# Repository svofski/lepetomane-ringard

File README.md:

# Pétomane ringard

A "simple" 3-voice "sound chip" with wavetables.

## Current status: 
 - [x] waiting for the first revision of PCB
 - [x] research implementation of USB MIDI
   - [ ] pico firmware in [sw/pico](sw/pico)
 - [x] audio level meter based on CH32V003
    - [CH32V003 specific notes](CH32V003-notes.md)
    - The code for the level meter is [here](wch-ch32v003/pio-arduino-ch32v003)
 - [x] assemble the PCB
   - [x] audio level meter
   - [x] Pi Pico host board
   - [x] main board
 - [ ] verification
   - [x] write a simple serial debug monitor
   - [x] 82c54 can be programmed, produces frequencies as expected
   - [x] counters U10, U11, U12 generate LSB addresses
     - this is hard to verify without a full logic probe (and even with one) but the counting period seems to be correct. I set ctr0 divider = 100, PITCHx256_A is 80kHz; pin U10.9 nRCO has short pulses at 312.5kHz, which is expected because 80e3/256 = 312.5
   - [ ] 82c55
   - [ ] MVOL DAC
   - [ ] WRMODE
   - [ ] LOOPEN_B (one-shot count on channel B)

## About this project

A never ending search of a simple chiptune synthesizer design that could have existed back in the 1980s. This design departs from the tech available to hobbyists in the 80s, but it's not too out there either. 

### Description in broad strokes

The master clock is 8MHz. Potentially 10MHz, but it would be pushing the capabilities of 82C54. The timer divides the main frequency and provides the pitch for the 3 channels. 

Waveforms are stored as samples in a ROM. This is essentially a short sample player. A sample is always 256 counts long, 8-bit waveform. For example, a sawtooth would be a sequence of numbers 0..255 stored in addresses 0..255. 
The ROM has 16 address bits, so there are 256 waveforms. This is how timbre and volume are set: simply by selecting 8 MSB of the sample address. It is possible to define just one waveshape and 256 amplitude levels, or for example 4 waveshapes and 64 amplitude levels for each one. Or several MSB bits could be reserved for selecting drum samples. It's a relatively flexible system.

One important remark. Because this is a frequency divider and the base frequency is only 8MHz, we don't get a good resolution if samples represent a single period. For decent musical resolution the waveforms will have to be squeezed to maybe 32 or 64 samples per period.

The 3 channels are time-multiplexed and sent to the two channels of DAC (TLC7258C) in a sequence. In order to provide a stereo mix, channels A/B/C/A/B/C are steered to channels L/L/R/L/R/R. Hopefully this will create an effect of a stereo mix where Left = A + 0.5B and Right = 0.5 + C.

There is a master volume which is just a second DAC providing reference voltage for the main DAC. If the main DAC is stopped, the master volume can be used to play back samples directly.

Channel B (central) can optionally stop after playing a sample once. This may be useful to play back short drum samples.

The MSB for channels A/B/C is set respectively in the registers A/B/C of 82C55. 

Because ROMs are a rare beast in 2024, K6X4008C1F SRAM is used instead. Only 64K of available address space is used. Loading is facilitated by the same 82C55 chip.

The external interface in the Pétomanesque tradition looks like a parallel port "ПУ" of Vector-06C, but in reality it's just a cursed three-row 2.54mm pin header. It is yet to be discovered whether this could ever be useful in a real computer or not. For now Raspberry Pi Pico will be used as a main driver for this board.

The complexity of this design surpasses the original expecation, yet remains within realm of possibility for a 80s design. SRAM in such quantities would have been wildly expensive back in the day, so a ROM could be used instead.

## Schematic/BOM
 * [https://github.com/svofski/lepetomane-ringard/tree/master/kicad/neopeto](https://kicanvas.org/?github=https%3A%2F%2Fgithub.com%2Fsvofski%2Flepetomane-ringard%2Ftree%2Fmaster%2Fkicad%2Fneopeto)
 * [ibom](https://svofski.github.io/lepetomane-ringard/ibom.html)

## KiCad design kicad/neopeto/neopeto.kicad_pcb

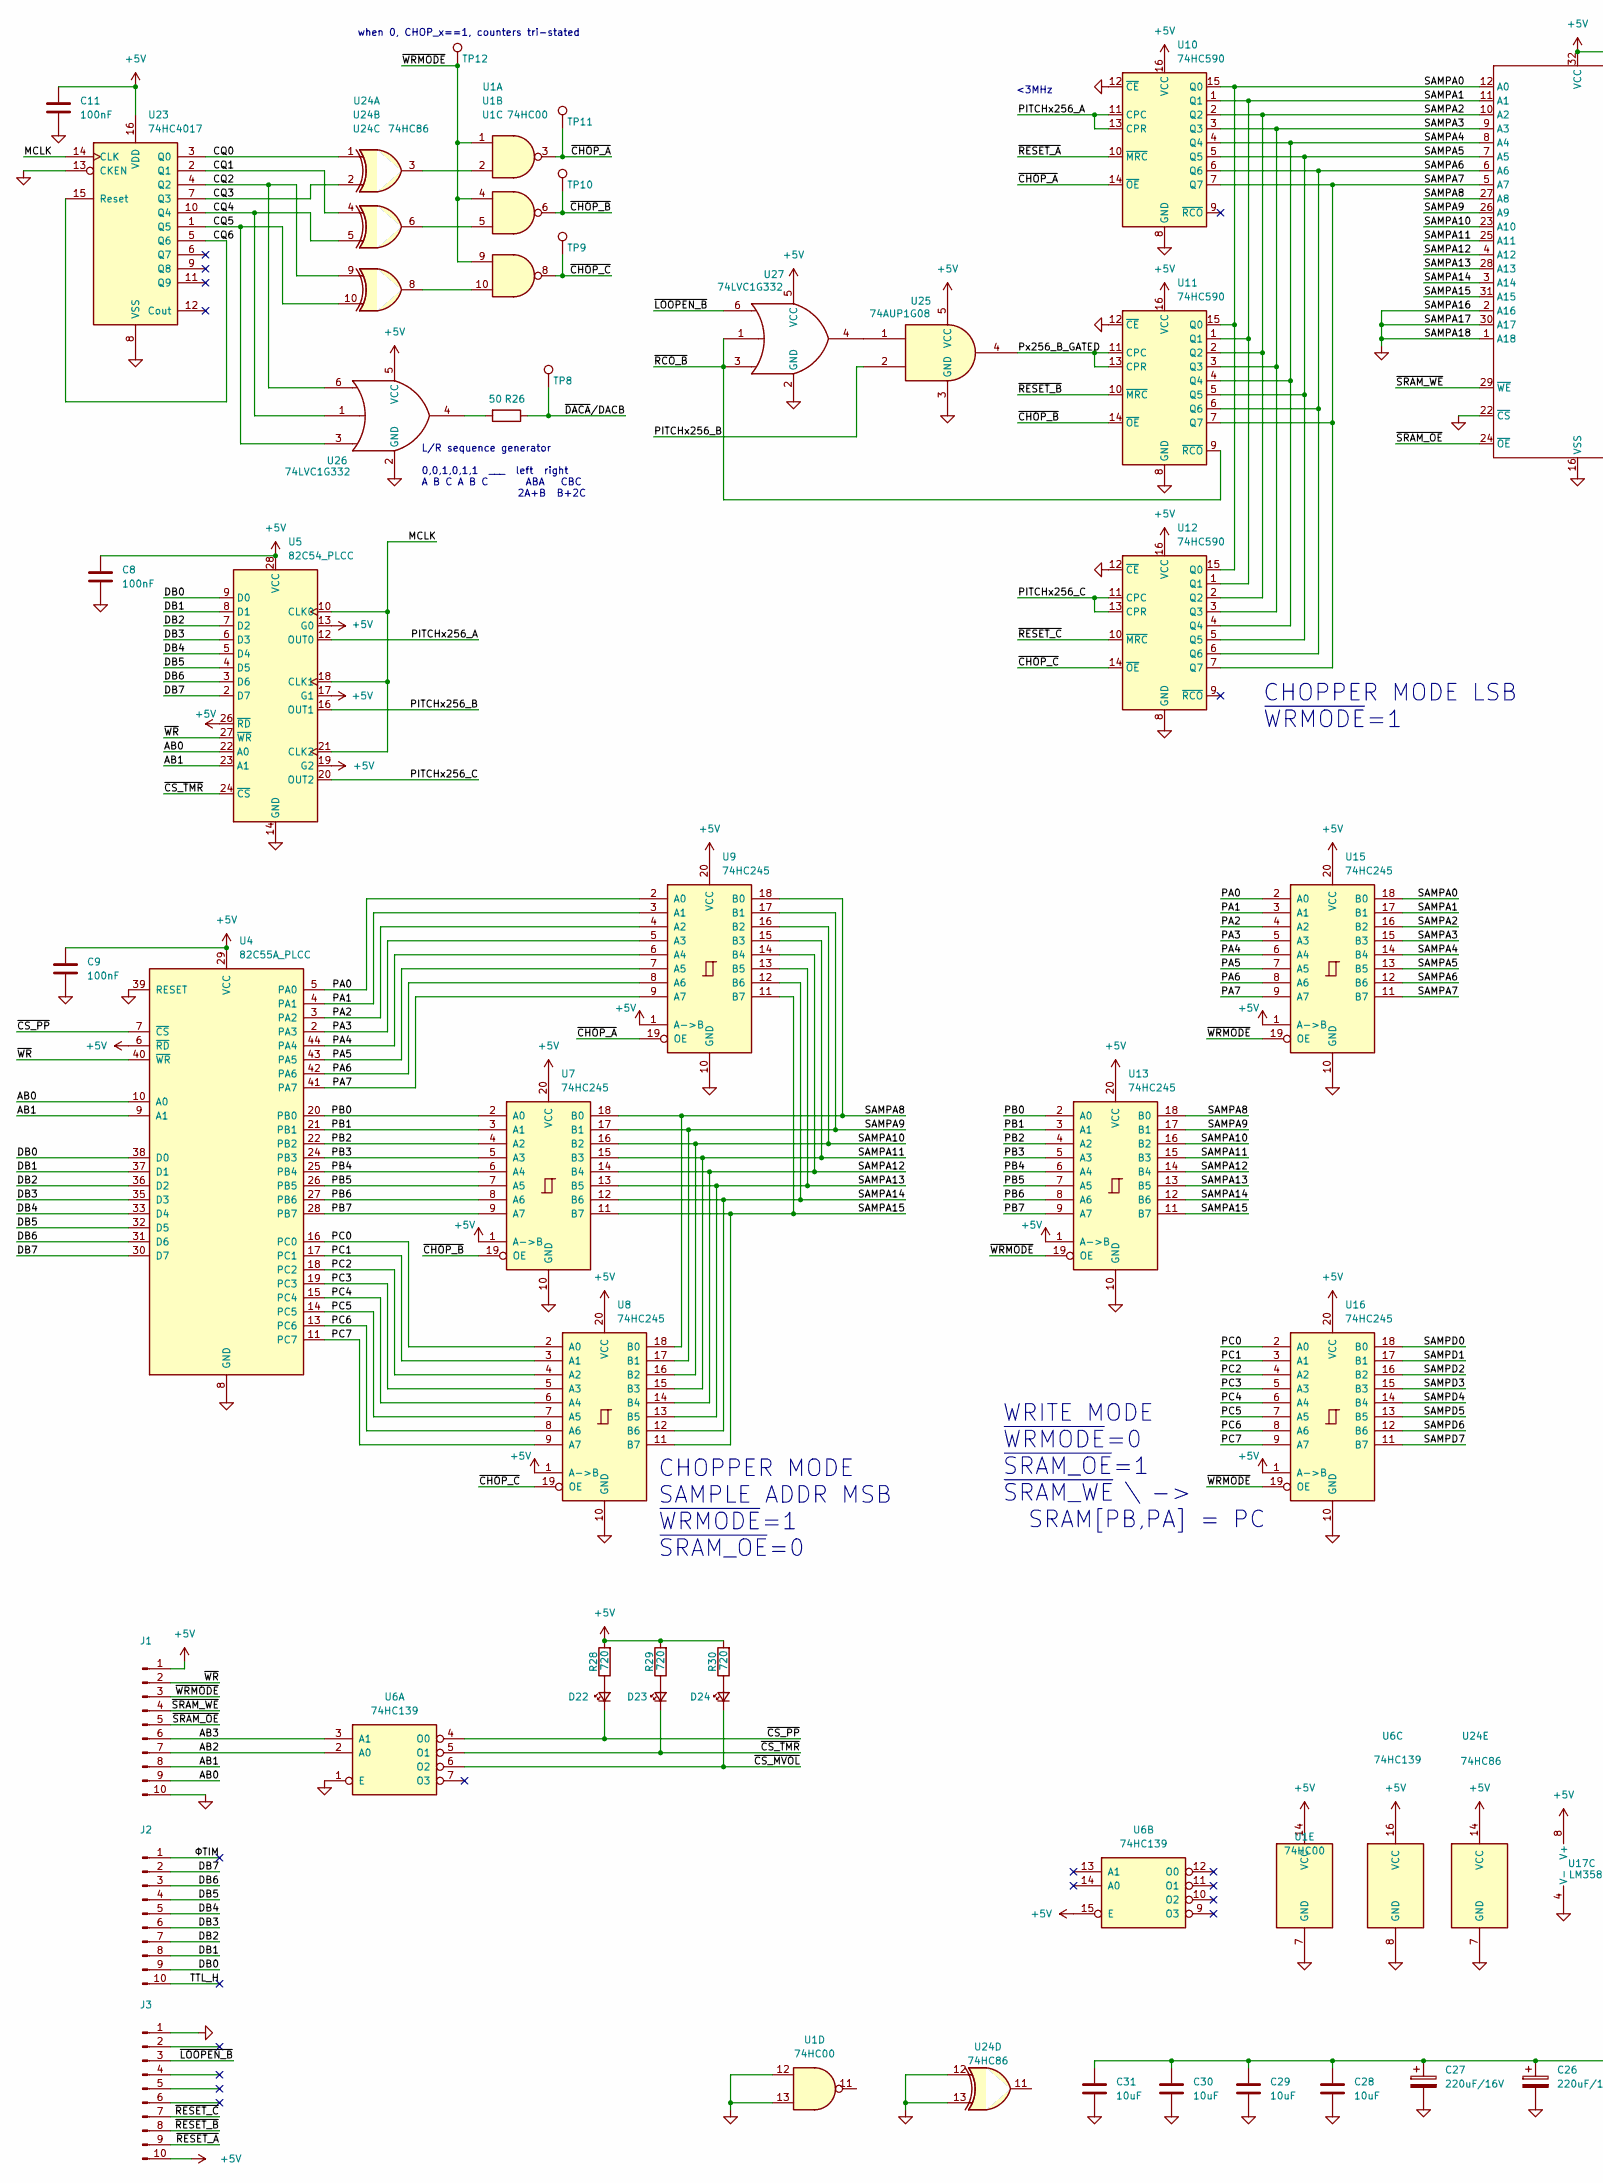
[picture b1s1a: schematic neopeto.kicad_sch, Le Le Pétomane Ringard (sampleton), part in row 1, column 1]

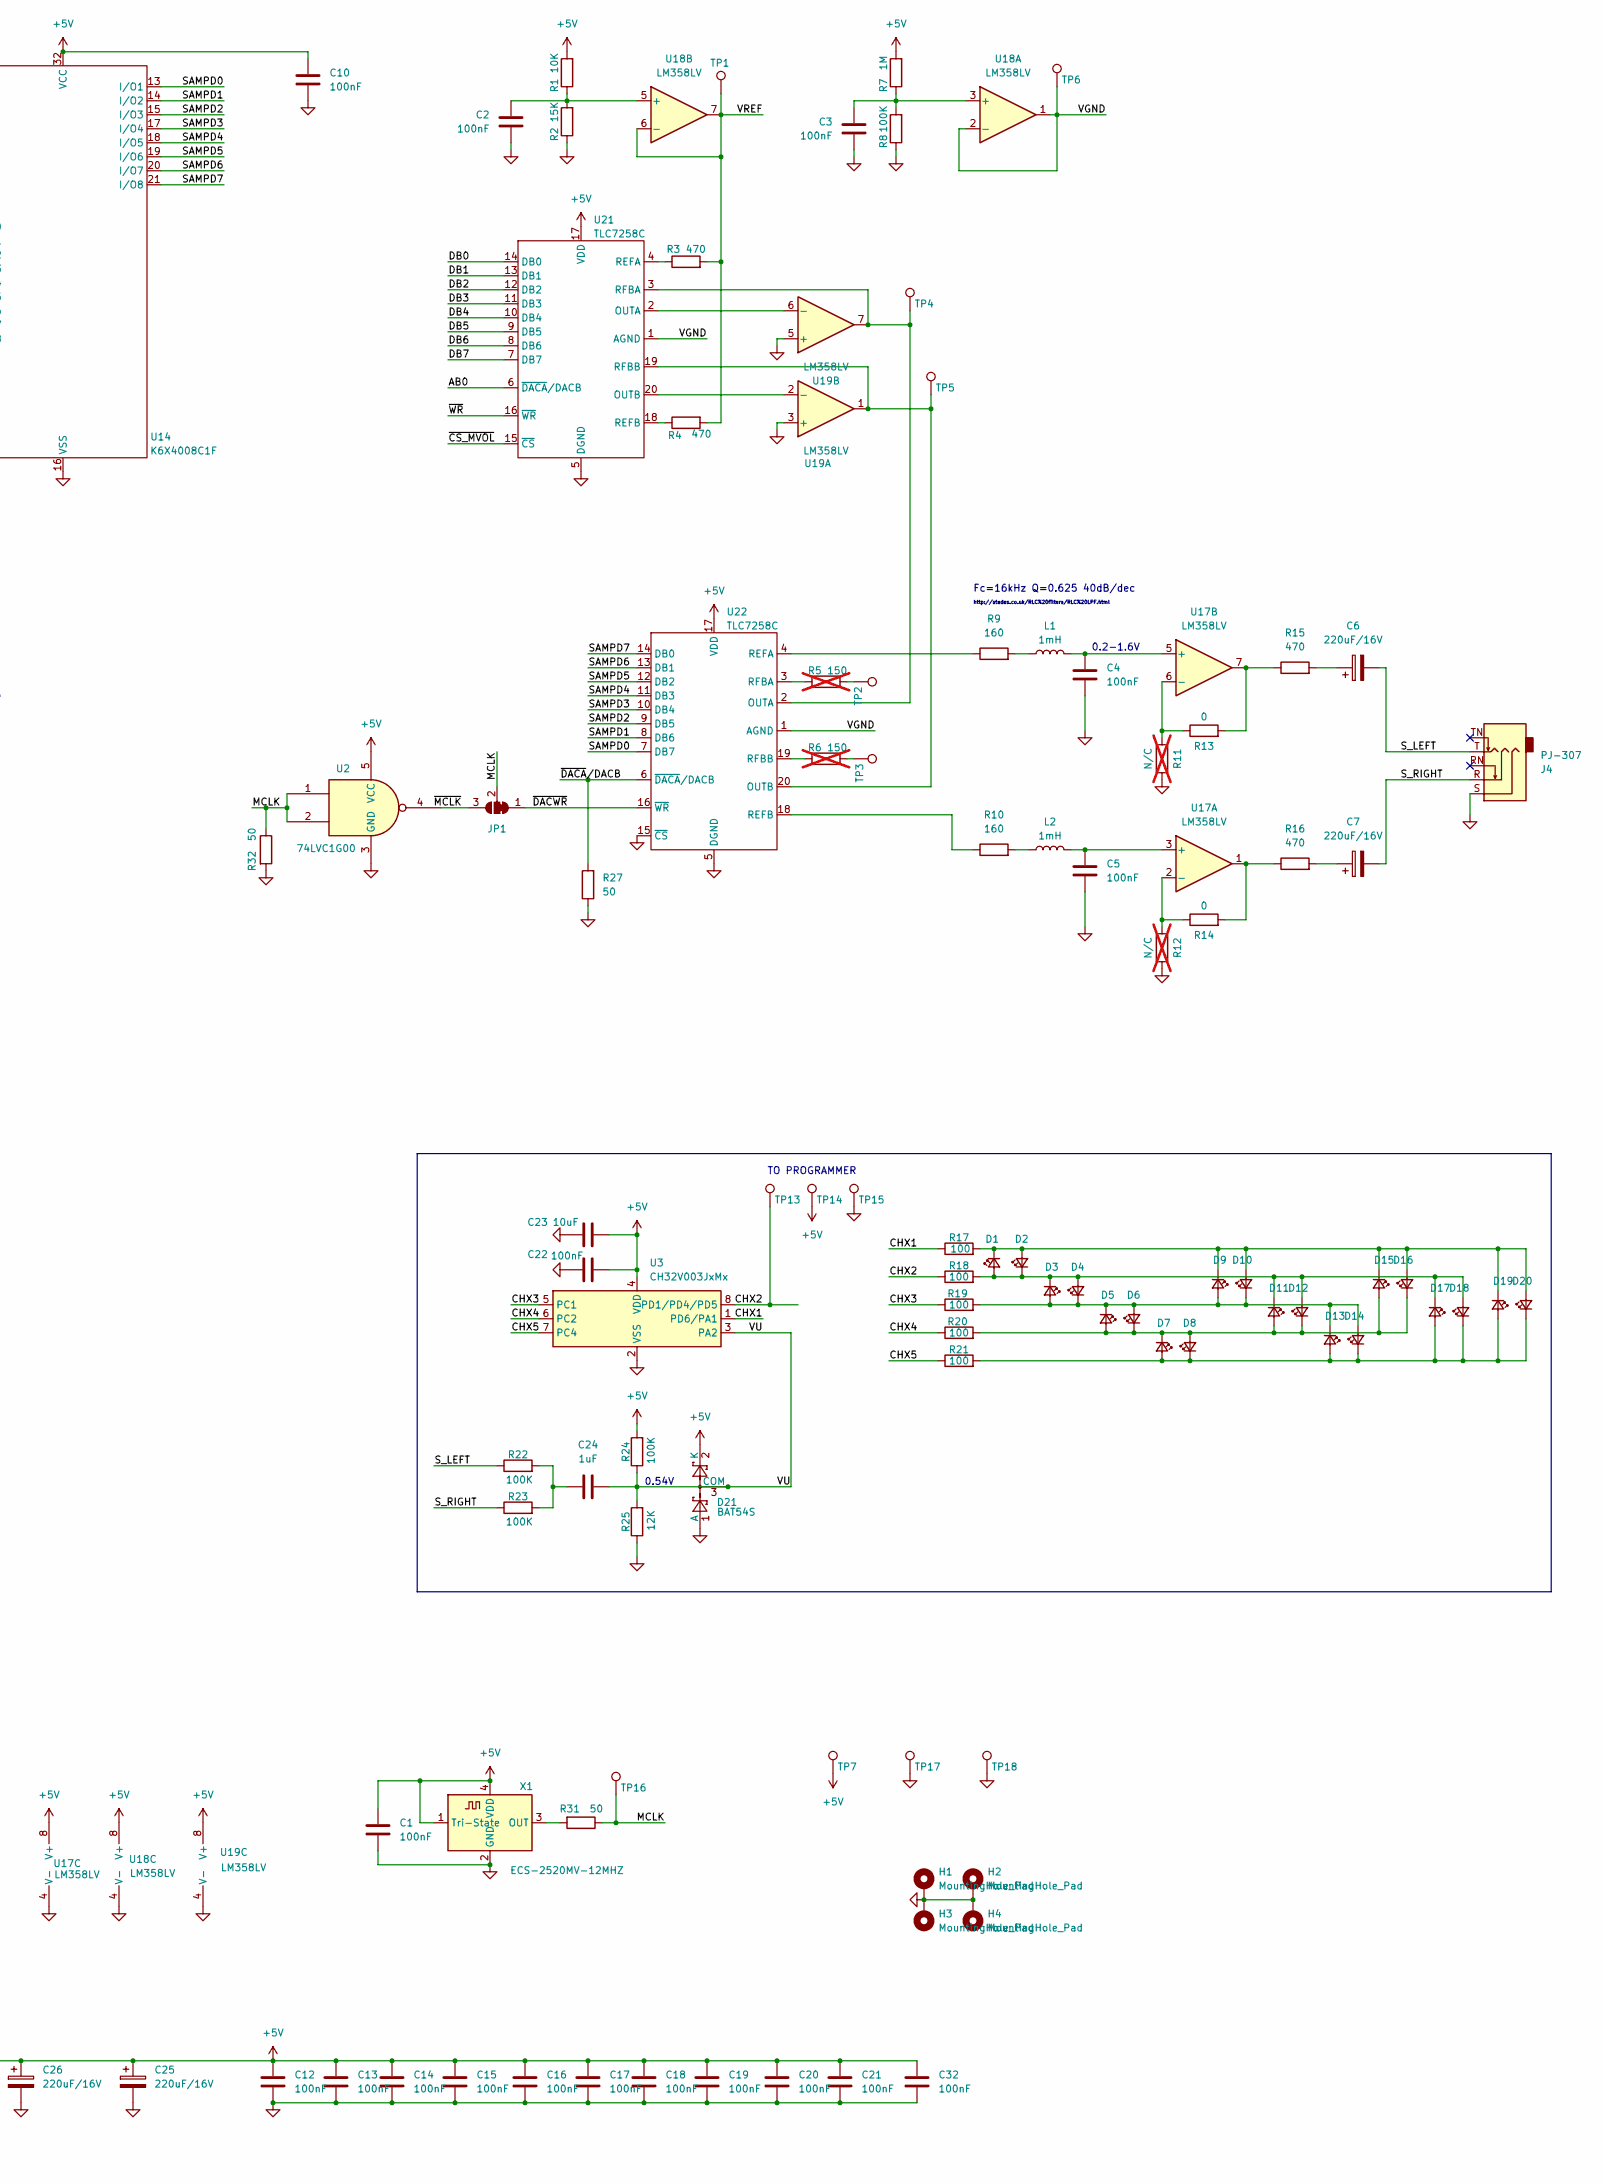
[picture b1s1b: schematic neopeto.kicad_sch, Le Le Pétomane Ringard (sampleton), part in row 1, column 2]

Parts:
C1, C2, C3, C8, C9, C10, C11, C12, C13, C14, C15, C16, C17, C18, C19, C20, C21, C22, C32: 100nF; C_0402_1005Metric
C4, C5: 100nF; C_0603_1608Metric
C6, C7: 220uF/16V; CP_Elec_6.3x7.7
C23, C28, C29, C30, C31: 10uF; C_0805_2012Metric
C24: 1uF; C_0805_2012Metric
C25, C26, C27: 220uF/16V; CP_EIA-7343-31_Kemet-D
D1, D2, D3, D4, D5, D6, D7, D8, D9, D10, D11, D12, D13, D14, D15, D16, D17, D18, D19, D20: LED_Small; LED_0402_1005Metric
D21: BAT54S; SOT-23
D22, D23, D24: LED_Small; LED_0603_1608Metric
H1, H2, H3, H4: MountingHole_Pad; MountingHole_3.2mm_M3_DIN965_Pad
J1, J2, J3: Conn_01x10_Pin; PinHeader_1x10_P2.54mm_Vertical
J4: PJ-307; Jack_3.5mm_CUI_SJ1-3525N_Horizontal
JP1: SolderJumper_3_Bridged12; SolderJumper-3_P1.3mm_Bridged12_RoundedPad1.0x1.5mm_NumberL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
L1, L2: 1mH; L_Radial_D7.2mm_P3.00mm_Murata_1700
R1: 10K; R_0805_2012Metric
R2: 15K; R_0805_2012Metric
R3, R4, R15, R16: 470; R_0805_2012Metric
R5, R6: 150; C_0603_1608Metric; not fitted
R7: 1M; R_0805_2012Metric
R8, R22, R23, R24: 100K; R_0805_2012Metric
R9, R10: 160; R_0805_2012Metric
R11, R12: N/C; R_0805_2012Metric; not fitted
R13, R14: 0; R_0805_2012Metric
R17, R18, R19, R20, R21: 100; R_0805_2012Metric
R25: 12K; R_0805_2012Metric
R26, R27, R31, R32: 50; R_0805_2012Metric
R28, R29, R30: 720; R_0805_2012Metric
TP1, TP2, TP3, TP4, TP5, TP6, TP7, TP8, TP9, TP10, TP11, TP12, TP13, TP14, TP15, TP16, TP17, TP18: TestPoint; TestPoint_Pad_D1.5mm
U1: 74HC00; SO-14_3.9x8.65mm_P1.27mm
U2: 74LVC1G00; SOT-353_SC-70-5
U3: CH32V003JxMx; SOP-8_3.9x4.9mm_P1.27mm
U4: 82C55A_PLCC; PLCC-44
U5: 82C54_PLCC; PLCC-28
U6: 74HC139; SOIC-16_3.9x9.9mm_P1.27mm
U7, U8, U9, U13, U15, U16: 74HC245; TSSOP-20_4.4x6.5mm_P0.65mm
U10, U11, U12: 74HC590; SOIC-16_3.9x9.9mm_P1.27mm
U14: K6X4008C1F; SSOP-32_11.305x20.495mm_P1.27mm
U17, U18, U19: LM358LV; SOIC-8_3.9x4.9mm_P1.27mm
U21, U22: TLC7258C; SOIC-20W_7.5x12.8mm_P1.27mm
U23: 74HC4017; SOIC-16_3.9x9.9mm_P1.27mm
U24: 74HC86; SO-14_3.9x8.65mm_P1.27mm
U25: 74AUP1G08; SOT-353_SC-70-5
U26, U27: 74LVC1G332; SOT-23-6
X1: ECS-2520MV-12MHZ; Oscillator_SMD_ECS_2520MV-xxx-xx-4Pin_2.5x2.0mm

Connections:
+5V: C1.2, C8.2, C9.2, C10.2, C11.2, C12.2, C13.2, C14.2, C15.2, C16.2, C17.2, C18.2, C19.2, C20.2, C21.2, C22.1, C23.1, C25.1, C26.1, C27.1, C28.2, C29.2, C30.2, C31.2, C32.2, D21.2 (K), J1.1, J3.10, R1.2, R7.2, R24.2, R28.2, R29.2, R30.2, TP7.1, TP14.1, U1.14 (VCC), U2.5 (VCC), U3.4 (VDD), U4.6 (~RD), U4.29 (VCC), U5.13 (G0), U5.17 (G1), U5.19 (G2), U5.26 (~RD), U5.28 (VCC), U6.15 (E), U6.16 (VCC), U7.1 (A->B), U7.20 (VCC), U8.1 (A->B), U8.20 (VCC), U9.1 (A->B), U9.20 (VCC), U10.16 (VCC), U11.16 (VCC), U12.16 (VCC), U13.1 (A->B), U13.20 (VCC), U14.32 (VCC), U15.1 (A->B), U15.20 (VCC), U16.1 (A->B), U16.20 (VCC), U17.8 (V+), U18.8 (V+), U19.8 (V+), U21.17 (VDD), U22.17 (VDD), U23.16 (VDD), U24.14 (VCC), U25.5 (VCC), U26.5 (VCC), U27.5 (VCC), X1.1 (Tri-State), X1.4 (VDD)
/AB0: J1.9, U4.10 (A0), U5.22 (A0), U21.6 (~DACA/DACB)
/AB1: J1.8, U4.9 (A1), U5.23 (A1)
/AB2: J1.7, U6.2 (A0)
/AB3: J1.6, U6.3 (A1)
/CHX1: R17.1, U3.1 (PD6/PA1)
/CHX2: R18.1, TP13.1, U3.8 (PD1/PD4/PD5)
/CHX3: R19.1, U3.5 (PC1)
/CHX4: R20.1, U3.6 (PC2)
/CHX5: R21.1, U3.7 (PC4)
/CQ0: U23.3 (Q0), U24.1
/CQ1: U23.2 (Q1), U24.4
/CQ2: U23.4 (Q2), U24.9, U26.6
/CQ3: U23.7 (Q3), U24.2
/CQ4: U23.10 (Q4), U24.5, U26.1
/CQ5: U23.1 (Q5), U24.10, U26.3
/CQ6: U23.5 (Q6), U23.15 (Reset)
/DB0: J2.9, U4.38 (D0), U5.9 (D0), U21.14 (DB0)
/DB1: J2.8, U4.37 (D1), U5.8 (D1), U21.13 (DB1)
/DB2: J2.7, U4.36 (D2), U5.7 (D2), U21.12 (DB2)
/DB3: J2.6, U4.35 (D3), U5.6 (D3), U21.11 (DB3)
/DB4: J2.5, U4.33 (D4), U5.5 (D4), U21.10 (DB4)
/DB5: J2.4, U4.32 (D5), U5.4 (D5), U21.9 (DB5)
/DB6: J2.3, U4.31 (D6), U5.3 (D6), U21.8 (DB6)
/DB7: J2.2, U4.30 (D7), U5.2 (D7), U21.7 (DB7)
/MCLK: JP1.2 (C), R31.1, R32.1, TP16.1, U2.1, U2.2, U5.10 (CLK0), U5.18 (CLK1), U5.21 (CLK2), U23.14 (CLK)
/PA0: U4.5 (PA0), U9.2 (A0), U15.2 (A0)
/PA1: U4.4 (PA1), U9.3 (A1), U15.3 (A1)
/PA2: U4.3 (PA2), U9.4 (A2), U15.4 (A2)
/PA3: U4.2 (PA3), U9.5 (A3), U15.5 (A3)
/PA4: U4.44 (PA4), U9.6 (A4), U15.6 (A4)
/PA5: U4.43 (PA5), U9.7 (A5), U15.7 (A5)
/PA6: U4.42 (PA6), U9.8 (A6), U15.8 (A6)
/PA7: U4.41 (PA7), U9.9 (A7), U15.9 (A7)
/PB0: U4.20 (PB0), U7.2 (A0), U13.2 (A0)
/PB1: U4.21 (PB1), U7.3 (A1), U13.3 (A1)
/PB2: U4.22 (PB2), U7.4 (A2), U13.4 (A2)
/PB3: U4.24 (PB3), U7.5 (A3), U13.5 (A3)
/PB4: U4.25 (PB4), U7.6 (A4), U13.6 (A4)
/PB5: U4.26 (PB5), U7.7 (A5), U13.7 (A5)
/PB6: U4.27 (PB6), U7.8 (A6), U13.8 (A6)
/PB7: U4.28 (PB7), U7.9 (A7), U13.9 (A7)
/PC0: U4.16 (PC0), U8.2 (A0), U16.2 (A0)
/PC1: U4.17 (PC1), U8.3 (A1), U16.3 (A1)
/PC2: U4.18 (PC2), U8.4 (A2), U16.4 (A2)
/PC3: U4.19 (PC3), U8.5 (A3), U16.5 (A3)
/PC4: U4.15 (PC4), U8.6 (A4), U16.6 (A4)
/PC5: U4.14 (PC5), U8.7 (A5), U16.7 (A5)
/PC6: U4.13 (PC6), U8.8 (A6), U16.8 (A6)
/PC7: U4.11 (PC7), U8.9 (A7), U16.9 (A7)
/PITCHx256_A: U5.12 (OUT0), U10.11 (CPC), U10.13 (CPR)
/PITCHx256_B: U5.16 (OUT1), U25.2
/PITCHx256_C: U5.20 (OUT2), U12.11 (CPC), U12.13 (CPR)
/Px256_B_GATED: U11.11 (CPC), U11.13 (CPR), U25.4
/SAMPA0: U10.15 (Q0), U11.15 (Q0), U12.15 (Q0), U14.12 (A0), U15.18 (B0)
/SAMPA1: U10.1 (Q1), U11.1 (Q1), U12.1 (Q1), U14.11 (A1), U15.17 (B1)
/SAMPA2: U10.2 (Q2), U11.2 (Q2), U12.2 (Q2), U14.10 (A2), U15.16 (B2)
/SAMPA3: U10.3 (Q3), U11.3 (Q3), U12.3 (Q3), U14.9 (A3), U15.15 (B3)
/SAMPA4: U10.4 (Q4), U11.4 (Q4), U12.4 (Q4), U14.8 (A4), U15.14 (B4)
/SAMPA5: U10.5 (Q5), U11.5 (Q5), U12.5 (Q5), U14.7 (A5), U15.13 (B5)
/SAMPA6: U10.6 (Q6), U11.6 (Q6), U12.6 (Q6), U14.6 (A6), U15.12 (B6)
/SAMPA7: U10.7 (Q7), U11.7 (Q7), U12.7 (Q7), U14.5 (A7), U15.11 (B7)
/SAMPA8: U7.18 (B0), U8.18 (B0), U9.18 (B0), U13.18 (B0), U14.27 (A8)
/SAMPA9: U7.17 (B1), U8.17 (B1), U9.17 (B1), U13.17 (B1), U14.26 (A9)
/SAMPA10: U7.16 (B2), U8.16 (B2), U9.16 (B2), U13.16 (B2), U14.23 (A10)
/SAMPA11: U7.15 (B3), U8.15 (B3), U9.15 (B3), U13.15 (B3), U14.25 (A11)
/SAMPA12: U7.14 (B4), U8.14 (B4), U9.14 (B4), U13.14 (B4), U14.4 (A12)
/SAMPA13: U7.13 (B5), U8.13 (B5), U9.13 (B5), U13.13 (B5), U14.28 (A13)
/SAMPA14: U7.12 (B6), U8.12 (B6), U9.12 (B6), U13.12 (B6), U14.3 (A14)
/SAMPA15: U7.11 (B7), U8.11 (B7), U9.11 (B7), U13.11 (B7), U14.31 (A15)
/SAMPD0: U14.13 (I/O1), U16.18 (B0), U22.7 (DB7)
/SAMPD1: U14.14 (I/O2), U16.17 (B1), U22.8 (DB6)
/SAMPD2: U14.15 (I/O3), U16.16 (B2), U22.9 (DB5)
/SAMPD3: U14.17 (I/O4), U16.15 (B3), U22.10 (DB4)
/SAMPD4: U14.18 (I/O5), U16.14 (B4), U22.11 (DB3)
/SAMPD5: U14.19 (I/O6), U16.13 (B5), U22.12 (DB2)
/SAMPD6: U14.20 (I/O7), U16.12 (B6), U22.13 (DB1)
/SAMPD7: U14.21 (I/O8), U16.11 (B7), U22.14 (DB0)
/S_LEFT: C6.2, J4.T, R22.1
/S_RIGHT: C7.2, J4.R, R23.1
/TTL_H: J2.10
/VGND: TP6.1, U18.1, U18.2 (-), U21.1 (AGND), U22.1 (AGND)
/VREF: R3.2, R4.2, TP1.1, U18.6 (-), U18.7
/VU: C24.1, D21.3 (COM), R24.1, R25.2, U3.3 (PA2)
/~CHOP_A: TP11.1, U1.3, U9.19 (OE), U10.14 (~OE)
/~CHOP_B: TP10.1, U1.6, U7.19 (OE), U11.14 (~OE)
/~CHOP_C: TP9.1, U1.8, U8.19 (OE), U12.14 (~OE)
/~CS_MVOL: D24.1 (K), U6.6 (O2), U21.15 (~CS)
/~CS_PP: D22.1 (K), U4.7 (~CS), U6.4 (O0)
/~CS_TMR: D23.1 (K), U5.24 (~CS), U6.5 (O1)
/~DACA/DACB: R26.1, R27.2, TP8.1, U22.6 (~DACA/DACB)
/~DACWR: JP1.1 (A), U22.16 (~WR)
/~LOOPEN_B: J3.3, U27.6
/~MCLK: JP1.3 (B), U2.4
/~RCO_B: U11.9 (~RCO), U27.1, U27.3
/~RESET_A: J3.9, U10.10 (~MRC)
/~RESET_B: J3.8, U11.10 (~MRC)
/~RESET_C: J3.7, U12.10 (~MRC)
/~SRAM_OE: J1.5, U14.24 (~OE)
/~SRAM_WE: J1.4, U14.29 (~WE)
/~WRMODE: J1.3, TP12.1, U1.1, U1.4, U1.9, U13.19 (OE), U15.19 (OE), U16.19 (OE)
/~WR: J1.2, U4.40 (~WR), U5.27 (~WR), U21.16 (~WR)
/ФTIM: J2.1
GND: C1.1, C2.1, C3.1, C4.1, C5.1, C8.1, C9.1, C10.1, C11.1, C12.1, C13.1, C14.1, C15.1, C16.1, C17.1, C18.1, C19.1, C20.1, C21.1, C22.2, C23.2, C25.2, C26.2, C27.2, C28.1, C29.1, C30.1, C31.1, C32.1, D21.1 (A), H1.1, H2.1, H3.1, H4.1, J1.10, J3.1, J4.S, R2.1, R8.1, R11.1, R12.1, R25.1, R27.1, R32.2, TP15.1, TP17.1, TP18.1, U1.7 (GND), U1.12, U1.13, U2.3 (GND), U3.2 (VSS), U4.8 (GND), U4.39 (RESET), U5.14 (GND), U6.1 (E), U6.8 (GND), U7.10 (GND), U8.10 (GND), U9.10 (GND), U10.8 (GND), U10.12 (~CE), U11.8 (GND), U11.12 (~CE), U12.8 (GND), U12.12 (~CE), U13.10 (GND), U14.1 (A18), U14.2 (A16), U14.16 (VSS), U14.22 (~CS), U14.30 (A17), U15.10 (GND), U16.10 (GND), U17.4 (V-), U18.4 (V-), U19.3 (+), U19.4 (V-), U19.5 (+), U21.5 (DGND), U22.5 (DGND), U22.15 (~CS), U23.8 (VSS), U23.13 (CKEN), U24.7 (GND), U24.12, U24.13, U25.3 (GND), U26.2 (GND), U27.2 (GND), X1.2 (GND)
unnamed: C6.1, R15.2
unnamed: C7.1, R16.2
unnamed: C24.2, R22.2, R23.2
unnamed: D1.2 (A), D2.1 (K), D3.1 (K), D4.2 (A), D11.1 (K), D12.2 (A), D17.1 (K), D18.2 (A), R18.2
unnamed: D1.1 (K), D2.2 (A), D9.1 (K), D10.2 (A), D15.1 (K), D16.2 (A), D19.1 (K), D20.2 (A), R17.2
unnamed: D3.2 (A), D4.1 (K), D5.1 (K), D6.2 (A), D9.2 (A), D10.1 (K), D13.1 (K), D14.2 (A), R19.2
unnamed: D5.2 (A), D6.1 (K), D7.1 (K), D8.2 (A), D11.2 (A), D12.1 (K), D15.2 (A), D16.1 (K), R20.2
unnamed: D7.2 (A), D8.1 (K), D13.2 (A), D14.1 (K), D17.2 (A), D18.1 (K), D19.2 (A), D20.1 (K), R21.2
unnamed: D22.2 (A), R28.1
unnamed: D23.2 (A), R29.1
unnamed: D24.2 (A), R30.1
unnamed: L1.1, R9.2
unnamed: L2.1, R10.2
unnamed: R5.2, TP2.1
unnamed: R6.2, TP3.1
unnamed: R13.2, R15.1, U17.7
unnamed: R14.2, R16.1, U17.1
unnamed: R26.2, U26.4
unnamed: U1.2, U24.3
unnamed: U1.5, U24.6
unnamed: U1.10, U24.8
unnamed: C5.2, L2.2, U17.3 (+)
unnamed: R12.2, R14.1, U17.2 (-)
unnamed: C4.2, L1.2, U17.5 (+)
unnamed: R11.2, R13.1, U17.6 (-)
unnamed: C3.2, R7.1, R8.2, U18.3 (+)
unnamed: C2.2, R1.1, R2.2, U18.5 (+)
unnamed: U19.2 (-), U21.20 (OUTB)
unnamed: U19.6 (-), U21.2 (OUTA)
unnamed: R3.1, U21.4 (REFA)
unnamed: R4.1, U21.18 (REFB)
unnamed: TP4.1, U19.7, U21.3 (RFBA), U22.2 (OUTA)
unnamed: TP5.1, U19.1, U21.19 (RFBB), U22.20 (OUTB)
unnamed: R9.1, U22.4 (REFA)
unnamed: R10.1, U22.18 (REFB)
unnamed: R5.1, U22.3 (RFBA)
unnamed: R6.1, U22.19 (RFBB)
unnamed: U25.1, U27.4
unnamed: R31.2, X1.3 (OUT)

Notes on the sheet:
CHOPPER MODE SAMPLE ADDR MSB ~{WRMODE}=1 ~{SRAM_OE}=0
http://stades.co.uk/RLC%20filters/RLC%20LPF.html
L/R sequence generator 0,0,1,0,1,1 ___ left right A B C A B C ABA CBC 2A+B B+2C
WRITE MODE ~{WRMODE}=0 ~{SRAM_OE}=1 ~{SRAM_WE} \ -> SRAM[PB,PA] = PC
<3MHz
TO PROGRAMMER
when 0, CHOP_x==1, counters tri-stated
CHOPPER MODE LSB ~{WRMODE}=1
0.2-1.6V
0.54V
Fc=16kHz Q=0.625 40dB/dec

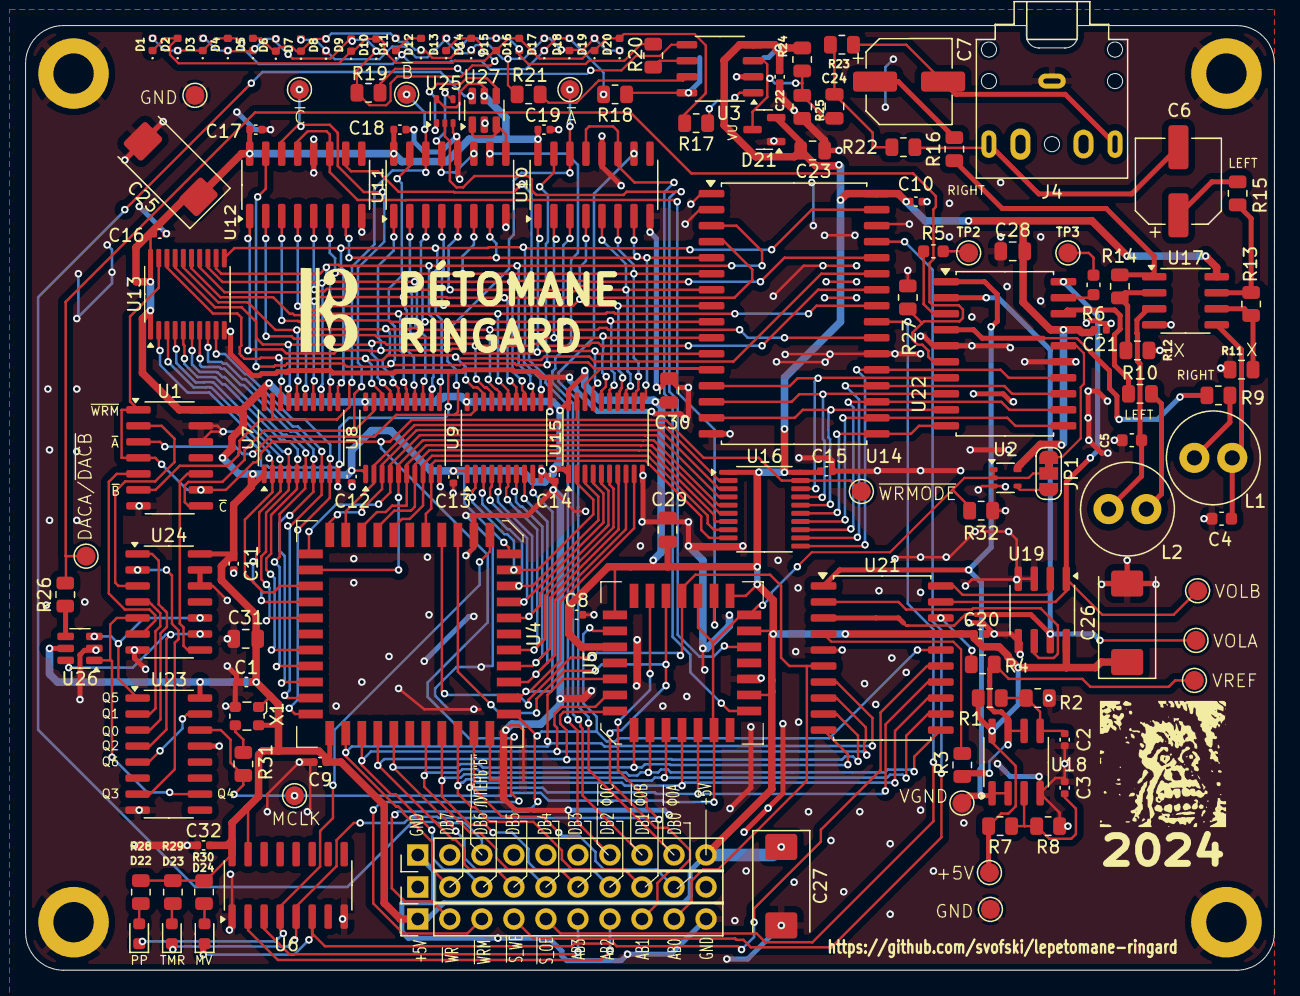
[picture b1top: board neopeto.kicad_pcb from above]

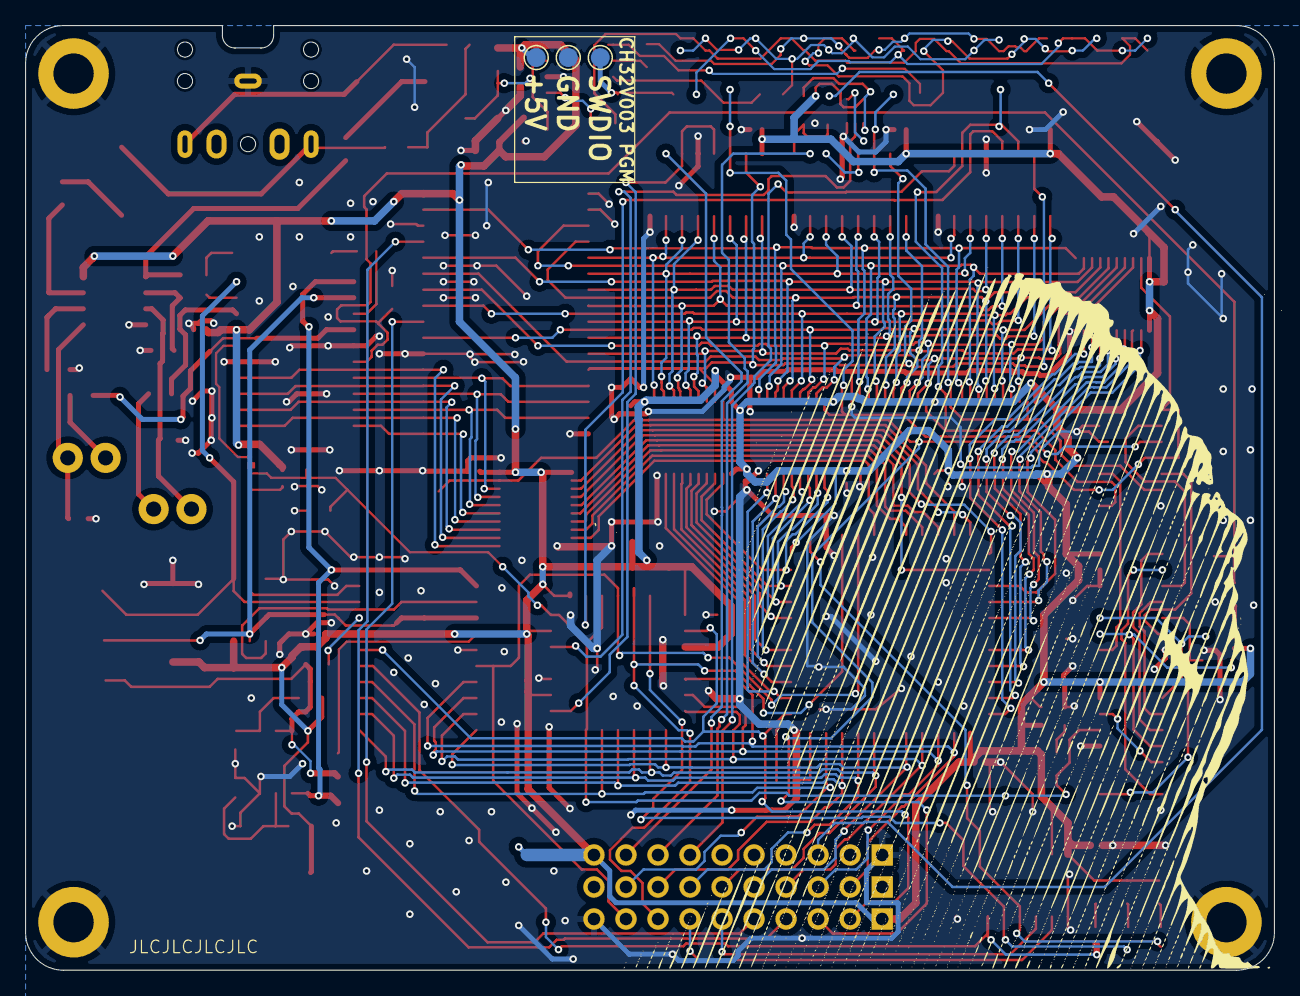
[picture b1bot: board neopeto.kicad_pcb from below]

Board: 2 copper layers, 99.1 x 74.9 mm, 144 parts (3 on the bottom side), 141 nets.

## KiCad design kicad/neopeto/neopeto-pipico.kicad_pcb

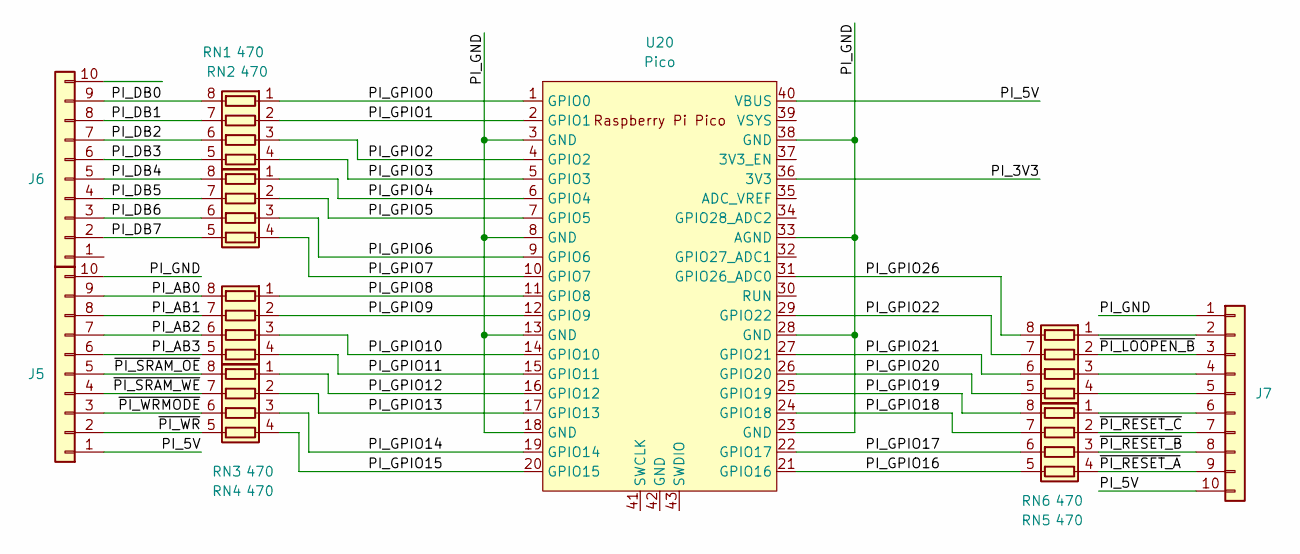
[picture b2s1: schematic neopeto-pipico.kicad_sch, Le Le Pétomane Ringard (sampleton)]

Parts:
J5, J6, J7: Conn_01x10; PinHeader_1x10_P2.54mm_Vertical
RN1, RN2, RN3, RN4, RN5, RN6: 470; R_Array_Concave_4x0603
U20: Pico; RPi_Pico_SMD_TH

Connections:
/PI_3V3: U20.36 (3V3)
/PI_5V: J5.1, J7.10, U20.40 (VBUS)
/PI_AB0: J5.9, RN3.8 (R1.2)
/PI_AB1: J5.8, RN3.7 (R2.2)
/PI_AB2: J5.7, RN3.6 (R3.2)
/PI_AB3: J5.6, RN3.5 (R4.2)
/PI_DB0: J6.9, RN1.8 (R1.2)
/PI_DB1: J6.8, RN1.7 (R2.2)
/PI_DB2: J6.7, RN1.6 (R3.2)
/PI_DB3: J6.6, RN1.5 (R4.2)
/PI_DB4: J6.5, RN2.8 (R1.2)
/PI_DB5: J6.4, RN2.7 (R2.2)
/PI_DB6: J6.3, RN2.6 (R3.2)
/PI_DB7: J6.2, RN2.5 (R4.2)
/PI_GND: J5.10, J7.1, U20.3 (GND), U20.8 (GND), U20.13 (GND), U20.18 (GND), U20.23 (GND), U20.28 (GND), U20.33 (AGND), U20.38 (GND)
/PI_GPIO0: RN1.1 (R1.1), U20.1 (GPIO0)
/PI_GPIO1: RN1.2 (R2.1), U20.2 (GPIO1)
/PI_GPIO2: RN1.3 (R3.1), U20.4 (GPIO2)
/PI_GPIO3: RN1.4 (R4.1), U20.5 (GPIO3)
/PI_GPIO4: RN2.1 (R1.1), U20.6 (GPIO4)
/PI_GPIO5: RN2.2 (R2.1), U20.7 (GPIO5)
/PI_GPIO6: RN2.3 (R3.1), U20.9 (GPIO6)
/PI_GPIO7: RN2.4 (R4.1), U20.10 (GPIO7)
/PI_GPIO8: RN3.1 (R1.1), U20.11 (GPIO8)
/PI_GPIO9: RN3.2 (R2.1), U20.12 (GPIO9)
/PI_GPIO10: RN3.3 (R3.1), U20.14 (GPIO10)
/PI_GPIO11: RN3.4 (R4.1), U20.15 (GPIO11)
/PI_GPIO12: RN4.1 (R1.1), U20.16 (GPIO12)
/PI_GPIO13: RN4.2 (R2.1), U20.17 (GPIO13)
/PI_GPIO14: RN4.3 (R3.1), U20.19 (GPIO14)
/PI_GPIO15: RN4.4 (R4.1), U20.20 (GPIO15)
/PI_GPIO16: RN5.5 (R4.2), U20.21 (GPIO16)
/PI_GPIO17: RN5.6 (R3.2), U20.22 (GPIO17)
/PI_GPIO18: RN5.7 (R2.2), U20.24 (GPIO18)
/PI_GPIO19: RN5.8 (R1.2), U20.25 (GPIO19)
/PI_GPIO20: RN6.5 (R4.2), U20.26 (GPIO20)
/PI_GPIO21: RN6.6 (R3.2), U20.27 (GPIO21)
/PI_GPIO22: RN6.7 (R2.2), U20.29 (GPIO22)
/PI_GPIO26: RN6.8 (R1.2), U20.31 (GPIO26_ADC0)
/~PI_LOOPEN_B: J7.3, RN6.2 (R2.1)
/~PI_RESET_A: J7.9, RN5.4 (R4.1)
/~PI_RESET_B: J7.8, RN5.3 (R3.1)
/~PI_RESET_C: J7.7, RN5.2 (R2.1)
/~PI_SRAM_OE: J5.5, RN4.8 (R1.2)
/~PI_SRAM_WE: J5.4, RN4.7 (R2.2)
/~PI_WRMODE: J5.3, RN4.6 (R3.2)
/~PI_WR: J5.2, RN4.5 (R4.2)
unnamed: J7.2, RN6.1 (R1.1)
unnamed: J7.4, RN6.3 (R3.1)
unnamed: J7.5, RN6.4 (R4.1)
unnamed: J7.6, RN5.1 (R1.1)

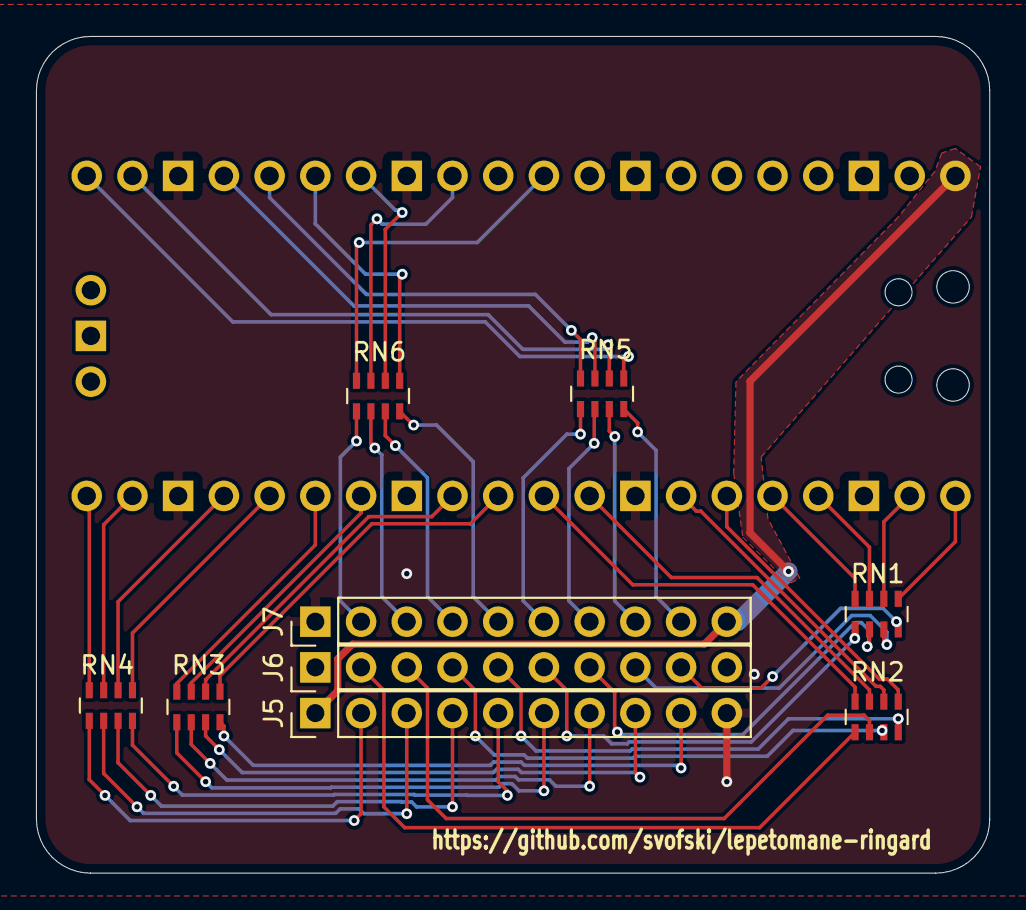
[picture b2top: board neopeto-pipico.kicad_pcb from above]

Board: 2 copper layers, 53.0 x 46.5 mm, 10 parts (1 on the bottom side), 50 nets.

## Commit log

2024-11-02 frist commit
2024-11-08 before separation
2024-11-09 as ordered
2024-11-09 pipico carrier borat added
2024-11-09 cleaned silkscreen rubbish, new screenshot
    it's so annoying that the script had to add LCSC part numbers to the
    silkscreen and I didn't notice it -- exactly because it's a production
    export script and you don't expect it to modify the files you send off.
    wtf really... so annoyed
2025-01-04 fixed missing connection to VU on ch32v003
2025-01-04 level meter source code added
2025-01-04 fixed includes
2025-01-04 includes fix
2025-01-04 readme for the level meter and picture
2025-01-04 configuration details
2025-01-04 layout and schematics for the docs
2025-01-04 datasheets
2025-01-04 FAST_SWITCHOFF, ops order in charlieplexing
    it is important in which order the operations are performed
    FAST_SWITCHOFF (enabled) just writes zeroes to ports C and D, makes them
    inputs
    switchOn first fast-switchoffs, then sets output values and then sets up
    pin directions. This minimizes parasitic leaks, although they are still
    slightly visible.
2025-01-08 update led resistor values
    470*2 / 20 makes for a rather dim display
    the leds are specified for 25mA at 1.6V
    100 ohm * 2 -> 17mA, bright enough not to look good next to other leds
    on my desk and on the same board
2025-01-08 pico firmware crib
    does:
    - builds (midi example that sends an arpeggio)
    - printf() to CDC stdio
    - reboots via baudrate 1200
2025-01-11 schematic update with scopes
2025-01-11 try oscilloscope in printable area
2025-01-12 test notes in the schematic + debug monitor
    debug monitor provides some basic commands to test the circuit
